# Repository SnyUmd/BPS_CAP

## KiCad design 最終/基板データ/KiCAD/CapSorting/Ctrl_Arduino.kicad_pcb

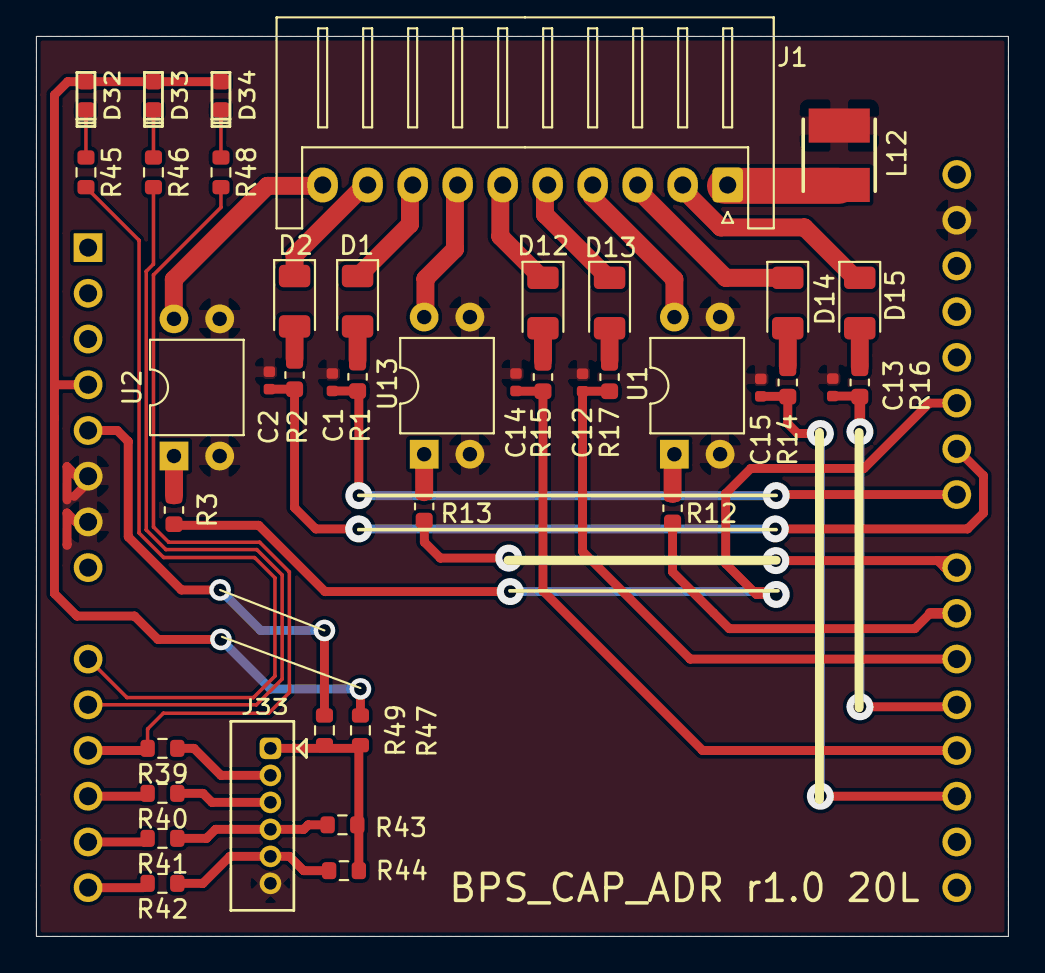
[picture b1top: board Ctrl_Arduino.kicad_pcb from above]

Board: 2 copper layers, 54.0 x 50.0 mm, 42 parts (1 on the bottom side), 45 nets.

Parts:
A12: Arduino_UNO_R3; Arduino_UNO_R2
C1, C2, C12, C13, C14, C15: 0.22u; R_0402_1005Metric
D1, D2, D12, D13, D14, D15: RB060M-60TR; D_1206_3216Metric
D32, D33, D34: LED; LED1608
J1: S10B-XH-A; JST_XH_S10B-XH-A_1x10_P2.50mm_Horizontal
J33: ZH_B6B-ZR
L12: 6.8uH(74404042068); INDPM4040X180N
R1, R2, R3, R12, R13, R14, R15, R16, R17: 1k; R_0603_1608Metric
R39, R40, R41, R42: 100; R_0603_1608Metric
R43, R44, R47: NC; R_0603_1608Metric
R45, R46, R48: 2.2k; R_0603_1608Metric
R49: 0; R_0603_1608Metric
U1, U2, U13: TLP785; DIP-4_W7.62mm

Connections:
+3V3: A12.4, D32.2, D33.2, D34.2, R47.2
+5V: A12.5, R49.2
AIR1_Y005: J1.10, U2.4
AIR2_Y006: J1.4, U1.4
AIR3_Y012: J1.7, U13.4
D16_A2: J33.2, R39.1
D17_A3: J33.3, R40.1
D18_A4: J33.4, R41.1, R43.1
D19_A5: J33.5, R42.1, R44.1
DeviceGND: J1.1, L12.2
GND: A12.6, A12.7, A12.29, C1.2, C2.2, C12.2, C13.2, C14.2, C15.2, J33.6, L12.1, U1.2, U1.3, U2.2, U2.3, U13.2, U13.3
unnamed: A12.9, R45.2
unnamed: A12.10, R46.2
unnamed: A12.11, R39.2, R48.2
unnamed: A12.12, R40.2
unnamed: A12.13, R41.2
unnamed: A12.14, R42.2
unnamed: A12.17, C15.1, R14.1
unnamed: A12.18, C14.1, R15.1
unnamed: A12.19, C13.1, R16.1
unnamed: A12.20, C12.1, R17.1
unnamed: A12.21, R12.1
unnamed: A12.22, R13.1
unnamed: A12.23, C1.1, R1.1
unnamed: A12.24, C2.1, R2.1
unnamed: A12.25, R3.1
unnamed: D1.2, R1.2
unnamed: D2.2, R2.2
unnamed: D12.2, R15.2
unnamed: D13.2, R17.2
unnamed: D14.2, R14.2
unnamed: D15.2, R16.2
unnamed: D32.1, R45.1
unnamed: D33.1, R46.1
unnamed: D34.1, R48.1
unnamed: J33.1, R43.2, R44.2, R47.1, R49.1
unnamed: R3.2, U2.1
unnamed: R12.2, U1.1
unnamed: R13.2, U13.1
PE_Camera_B17: D14.1, J1.3
PassSensor_Area1: D2.1, J1.9
PassSensor_Area2: D15.1, J1.2
PassSensor_Area3: D13.1, J1.5
Sensor1: D1.1, J1.8
WhiteSensor: D12.1, J1.6

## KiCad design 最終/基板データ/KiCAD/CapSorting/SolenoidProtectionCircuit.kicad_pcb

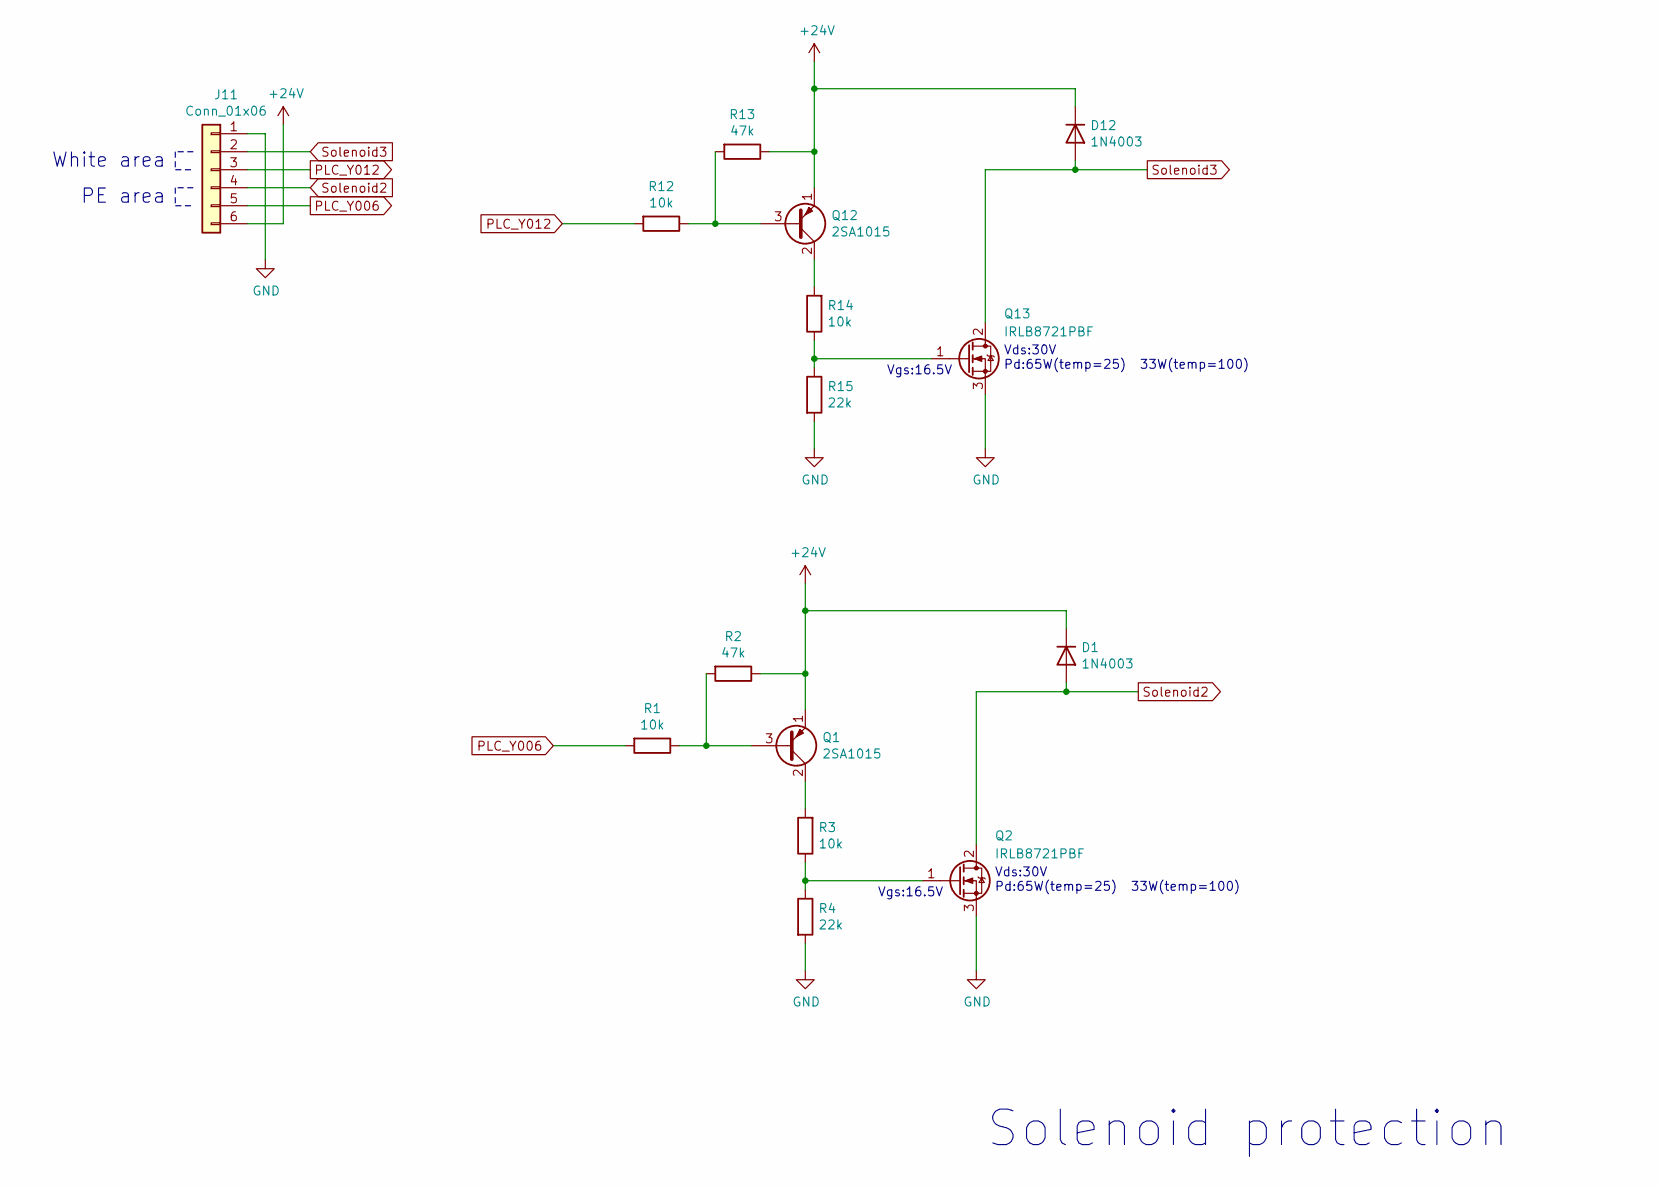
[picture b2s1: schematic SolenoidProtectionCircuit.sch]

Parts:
D1, D12: 1N4003; D_DO-41_SOD81_P10.16mm_Horizontal
J11: Conn_01x06; JST_XH_S6B-XH-A_1x06_P2.50mm_Horizontal
Q1, Q12: 2SA1015; TO-92_Inline
Q2, Q13: IRLB8721PBF; IRLB8721PBF-2
R1, R3, R12, R14: 10k; R_0603_1608Metric
R2, R13: 47k; R_0603_1608Metric
R4, R15: 22k; R_0603_1608Metric

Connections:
+24V: D1.1 (K), D12.1 (K), J11.6, Q1.1 (E), Q12.1 (E), R2.1, R13.1
GND: J11.1, Q2.3 (S), Q13.3 (S), R4.2, R15.2
unnamed: Q1.2 (C), R3.2
unnamed: Q1.3 (B), R1.1, R2.2
unnamed: Q2.1 (G), R3.1, R4.1
unnamed: Q12.2 (C), R14.2
unnamed: Q12.3 (B), R12.1, R13.2
unnamed: Q13.1 (G), R14.1, R15.1
PLC_Y006: J11.3, R12.2
PLC_Y012: J11.5, R1.2
Solenoid1: D12.2 (A), J11.2, Q13.2 (D)
Solenoid2: D1.2 (A), J11.4, Q2.2 (D)

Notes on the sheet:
Solenoid protection
Vgs:16.5V
Vds:30V Pd:65W(temp=25) 33W(temp=100)
PE area
White area

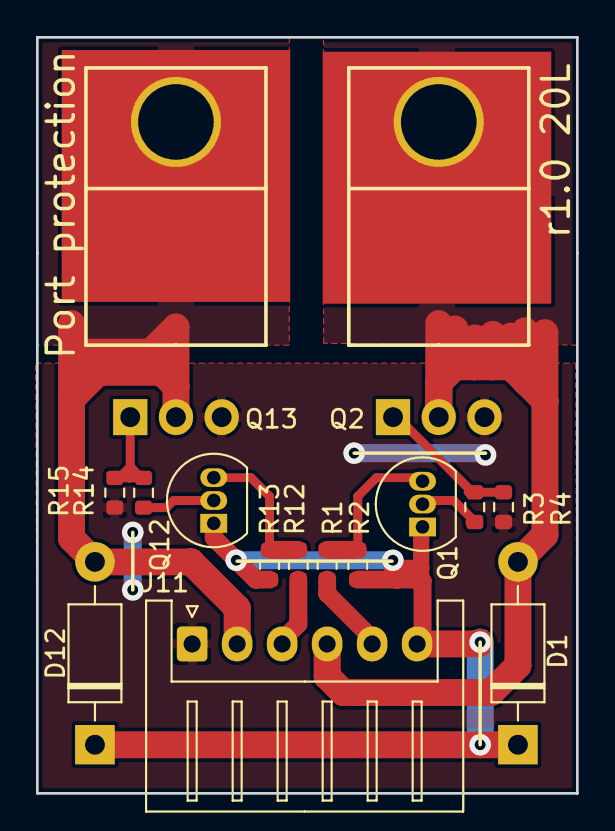
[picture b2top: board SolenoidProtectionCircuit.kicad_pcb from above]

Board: 2 copper layers, 30.0 x 42.0 mm, 15 parts (0 on the bottom side), 12 nets.

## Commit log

2020-12-16 no message
2020-12-16 Timer参考ページ追加
2020-12-26 LED追加 Init.h追加 Def.h追加 Timer.h中身追加
2020-12-26 コード整理
2020-12-26 Revert "コード整理"
    This reverts commit d1ffeea414ec79e1700171f627adf88594746345.
2020-12-26 Revert "Revert "コード整理""
    This reverts commit c9349d9d4074911fd6129b90079a3e5a84214b4a.
2020-12-28 初期メッセージ追加
2022-09-24 最終版を追加
